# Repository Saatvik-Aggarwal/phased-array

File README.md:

# phased-array
Simulation and design of a phased array for wireless power transmission

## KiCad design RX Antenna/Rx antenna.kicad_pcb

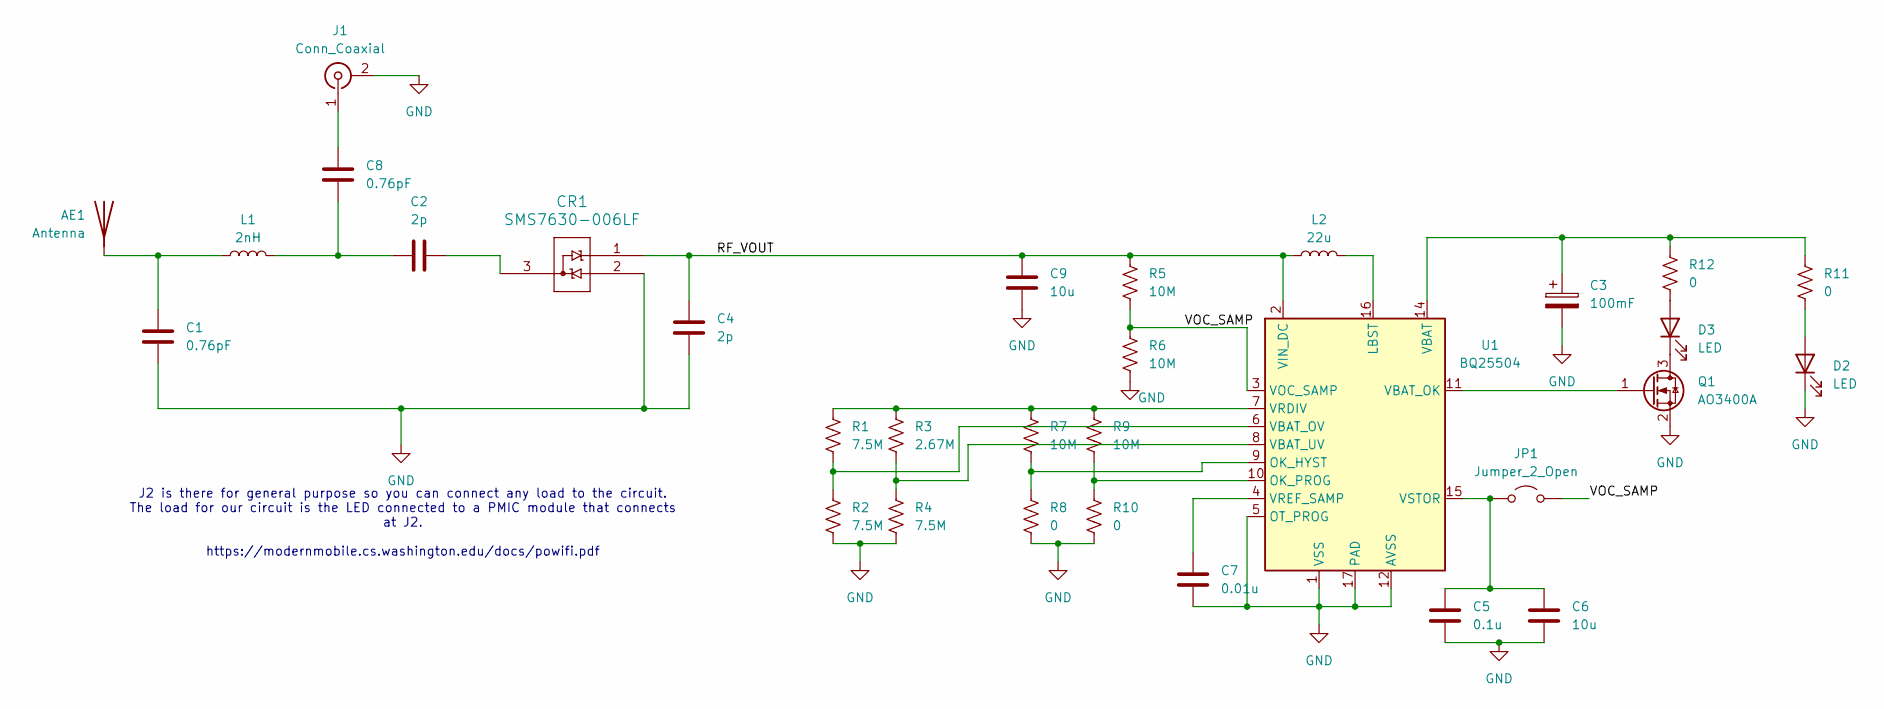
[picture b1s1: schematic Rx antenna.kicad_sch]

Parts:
AE1: Antenna; AperturePatch
C1: 0.76pF; C_0201_0603Metric_Pad0.64x0.40mm_HandSolder
C2, C4: 2p; C_0201_0603Metric_Pad0.64x0.40mm_HandSolder
C3: 100mF; CP_Radial_D10.0mm_P5.00mm
C5: 0.1u; C_0603_1608Metric_Pad1.08x0.95mm_HandSolder
C6, C9: 10u; C_0603_1608Metric_Pad1.08x0.95mm_HandSolder
C7: 0.01u; C_0603_1608Metric_Pad1.08x0.95mm_HandSolder
C8: 0.76pF; C_0201_branch
CR1: SMS7630-006LF; SOT-23
D2, D3: LED; LED_0603_1608Metric_Pad1.05x0.95mm_HandSolder
J1: Conn_Coaxial; U.FL_Hirose_U.FL-R-SMT-1_Vertical
JP1: Jumper_2_Open; SolderJumper-2_P1.3mm_Open_RoundedPad1.0x1.5mm
L1: 2nH; L_0201_0603Metric_Pad0.64x0.40mm_HandSolder
L2: 22u; L_1210_3225Metric_Pad1.42x2.65mm_HandSolder
Q1: AO3400A; SOT-23
R1, R2, R4: 7.5M; R_0603_1608Metric_Pad0.98x0.95mm_HandSolder
R3: 2.67M; R_0603_1608Metric_Pad0.98x0.95mm_HandSolder
R5, R6, R7, R9: 10M; R_0603_1608Metric_Pad0.98x0.95mm_HandSolder
R8, R10, R11, R12: 0; R_0603_1608Metric_Pad0.98x0.95mm_HandSolder
U1: BQ25504; VQFN-16-1EP_3x3mm_P0.5mm_EP1.68x1.68mm

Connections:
/RF_VOUT: C4.1, C9.1, CR1.1, L2.1, R5.1, U1.2 (VIN_DC)
/VOC_SAMP: JP1.2 (B), R5.2, R6.1, U1.3 (VOC_SAMP)
GND: C1.2, C3.2, C4.2, C5.2, C6.2, C7.2, C9.2, CR1.2, D2.1 (K), J1.2 (Ext), Q1.2 (S), R2.2, R4.2, R6.2, R8.2, R10.2, U1.1 (VSS), U1.5 (OT_PROG), U1.12 (AVSS), U1.13 (VSS), U1.17 (PAD)
unnamed: AE1.1 (A_1), C1.1, L1.1
unnamed: C2.1, C8.1, L1.2
unnamed: C2.2, CR1.3
unnamed: D2.2 (A), R11.2
unnamed: D3.2 (A), R12.2
unnamed: D3.1 (K), Q1.3 (D)
unnamed: C8.2, J1.1 (In)
unnamed: C5.1, C6.1, JP1.1 (A), U1.15 (VSTOR)
unnamed: Q1.1 (G), U1.11 (VBAT_OK)
unnamed: L2.2, U1.16 (LBST)
unnamed: R7.2, R8.1, U1.9 (OK_HYST)
unnamed: R9.2, R10.1, U1.10 (OK_PROG)
unnamed: C3.1, R11.1, R12.1, U1.14 (VBAT)
unnamed: R1.2, R2.1, U1.6 (VBAT_OV)
unnamed: R3.2, R4.1, U1.8 (VBAT_UV)
unnamed: R1.1, R3.1, R7.1, R9.1, U1.7 (VRDIV)
unnamed: C7.1, U1.4 (VREF_SAMP)

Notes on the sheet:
J2 is there for general purpose so you can connect any load to the circuit. The load for our circuit is the LED connected to a PMIC module that connects at J2. https://modernmobile.cs.washington.edu/docs/powifi.pdf

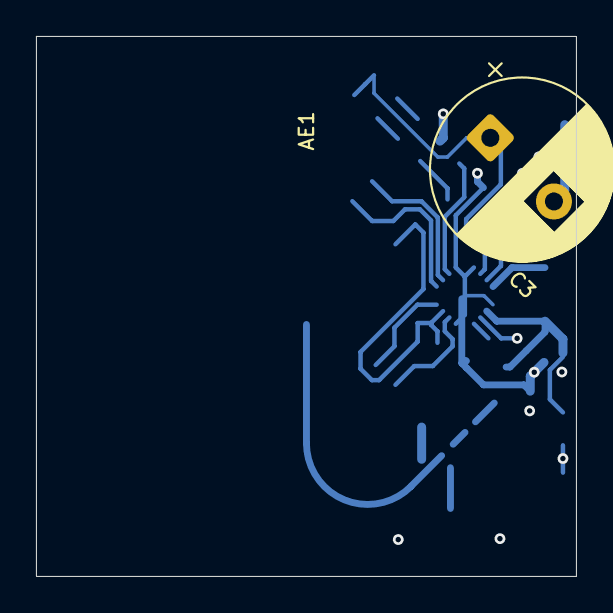
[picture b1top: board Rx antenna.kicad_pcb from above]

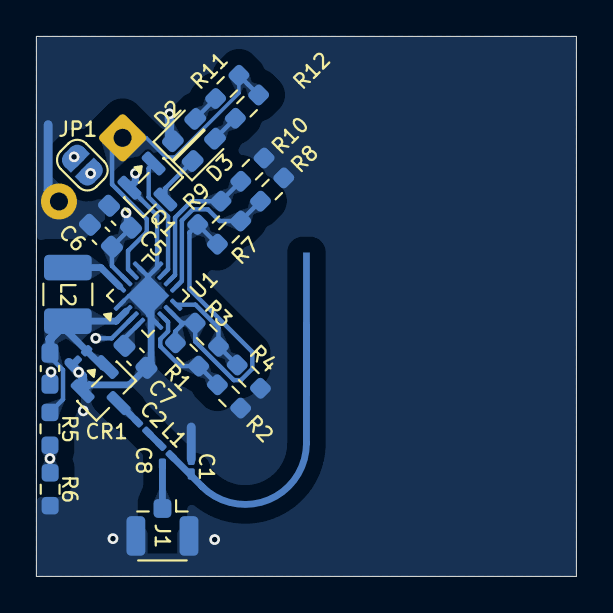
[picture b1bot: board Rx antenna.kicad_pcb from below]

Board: 4 copper layers, 30.0 x 30.0 mm, 31 parts (29 on the bottom side), 20 nets.

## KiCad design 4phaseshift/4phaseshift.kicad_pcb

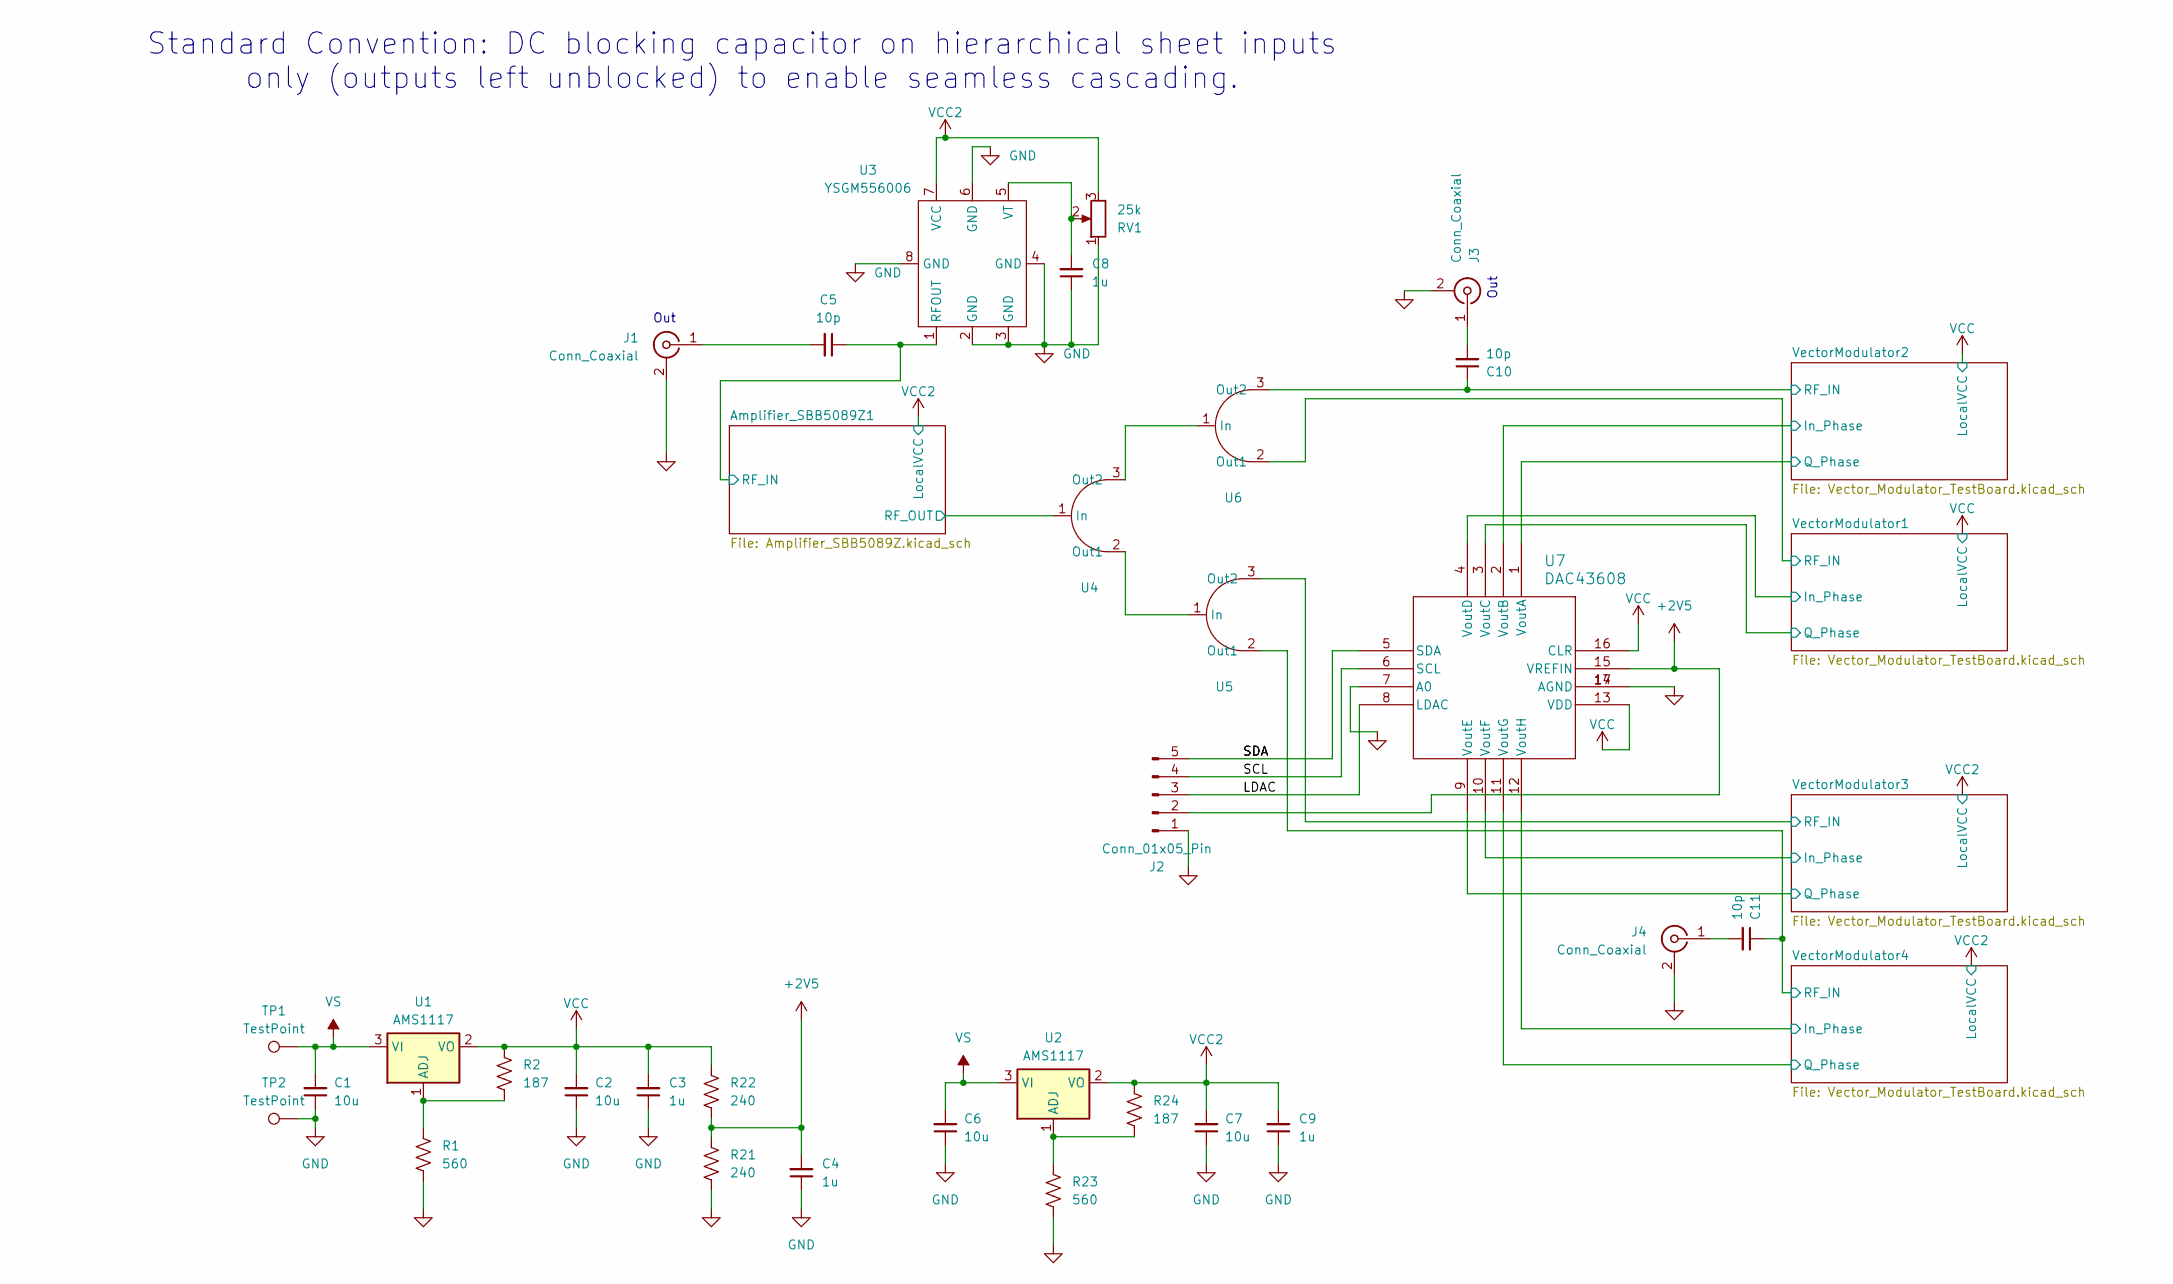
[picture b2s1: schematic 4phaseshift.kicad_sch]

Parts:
C1, C2, C6, C7: 10u; C_0603_1608Metric_Pad1.08x0.95mm_HandSolder
C3, C4, C8, C9: 1u; C_0603_1608Metric_Pad1.08x0.95mm_HandSolder
C5, C10, C11: 10p; C_0201_branch
J1, J3, J4: Conn_Coaxial; U.FL_Hirose_U.FL-R-SMT-1_Vertical
J2: Conn_01x05_Pin; PinHeader_1x05_P2.54mm_Vertical
R1, R23: 560; R_0603_1608Metric_Pad0.98x0.95mm_HandSolder
R2, R24: 187; R_0603_1608Metric_Pad0.98x0.95mm_HandSolder
R21, R22: 240; R_0603_1608Metric_Pad0.98x0.95mm_HandSolder
RV1: 25k; Potentiometer_Bourns_3386X_Horizontal
TP1, TP2: TestPoint; PinHeader_1x01_P2.54mm_Vertical
U1, U2: AMS1117; SOT-223-3_TabPin2
U3: YSGM556006; Innotion9070
U4, U5, U6: T_Splitter
U7: DAC43608; WQFN-16-1EP_3x3mm_P0.5mm_EP1.68x1.68mm

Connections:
+2V5: C4.2, J2.2, R21.1, R22.2, U7.15 (VREFIN)
/Amplifier_SBB5089Z1/RF_IN: C5.1, U3.1 (RFOUT); also elsewhere on the board
/Amplifier_SBB5089Z1/RF_OUT: U4.1 (In); also elsewhere on the board
/LDAC: J2.3, U7.8 (LDAC)
/SCL: J2.4, U7.6 (SCL)
/VectorModulator1/IBBN: U7.4 (VoutD); also elsewhere on the board
/VectorModulator1/QBBN: U7.3 (VoutC); also elsewhere on the board
/VectorModulator1/RF_IN: U6.2 (Out1); also elsewhere on the board
/VectorModulator2/IBBN: U7.2 (VoutB); also elsewhere on the board
/VectorModulator2/QBBN: U7.1 (VoutA); also elsewhere on the board
/VectorModulator2/RF_IN: C10.1, U6.3 (Out2); also elsewhere on the board
/VectorModulator3/IBBN: U7.10 (VoutF); also elsewhere on the board
/VectorModulator3/QBBN: U7.9 (VoutE); also elsewhere on the board
/VectorModulator3/RF_IN: U5.3 (Out2); also elsewhere on the board
/VectorModulator4/IBBN: U7.12 (VoutH); also elsewhere on the board
/VectorModulator4/QBBN: U7.11 (VoutG); also elsewhere on the board
/VectorModulator4/RF_IN: C11.1, U5.2 (Out1); also elsewhere on the board
GND: C1.1, C2.1, C3.1, C4.1, C6.1, C7.1, C8.1, C9.1, J1.2 (Ext), J2.1, J3.2 (Ext), J4.2 (Ext), R1.2, R21.2, R23.2, RV1.1, TP2.1, U3.2 (GND), U3.3 (GND), U3.4 (GND), U3.6 (GND), U3.8 (GND), U7.7 (A0), U7.14 (AGND), U7.17 (AGND); also elsewhere on the board
unnamed: C5.2, J1.1 (In)
unnamed: J2.5, U7.5 (SDA)
unnamed: C10.2, J3.1 (In)
unnamed: C11.2, J4.1 (In)
unnamed: R1.1, R2.2, U1.1 (ADJ)
unnamed: R23.1, R24.2, U2.1 (ADJ)
unnamed: C8.2, RV1.2, U3.5 (VT)
unnamed: U4.2 (Out1), U5.1 (In)
unnamed: U4.3 (Out2), U6.1 (In)
VCC: C2.2, C3.2, R2.1, R22.1, U1.2 (VO), U7.13 (VDD), U7.16 (CLR); also elsewhere on the board
VCC2: C7.2, C9.2, R24.1, RV1.3, U2.2 (VO), U3.7 (VCC); also elsewhere on the board
VS: C1.2, C6.2, TP1.1, U1.3 (VI), U2.3 (VI); also elsewhere on the board

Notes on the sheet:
Out
Standard Convention: DC blocking capacitor on hierarchical sheet inputs only (outputs left unblocked) to enable seamless cascading.

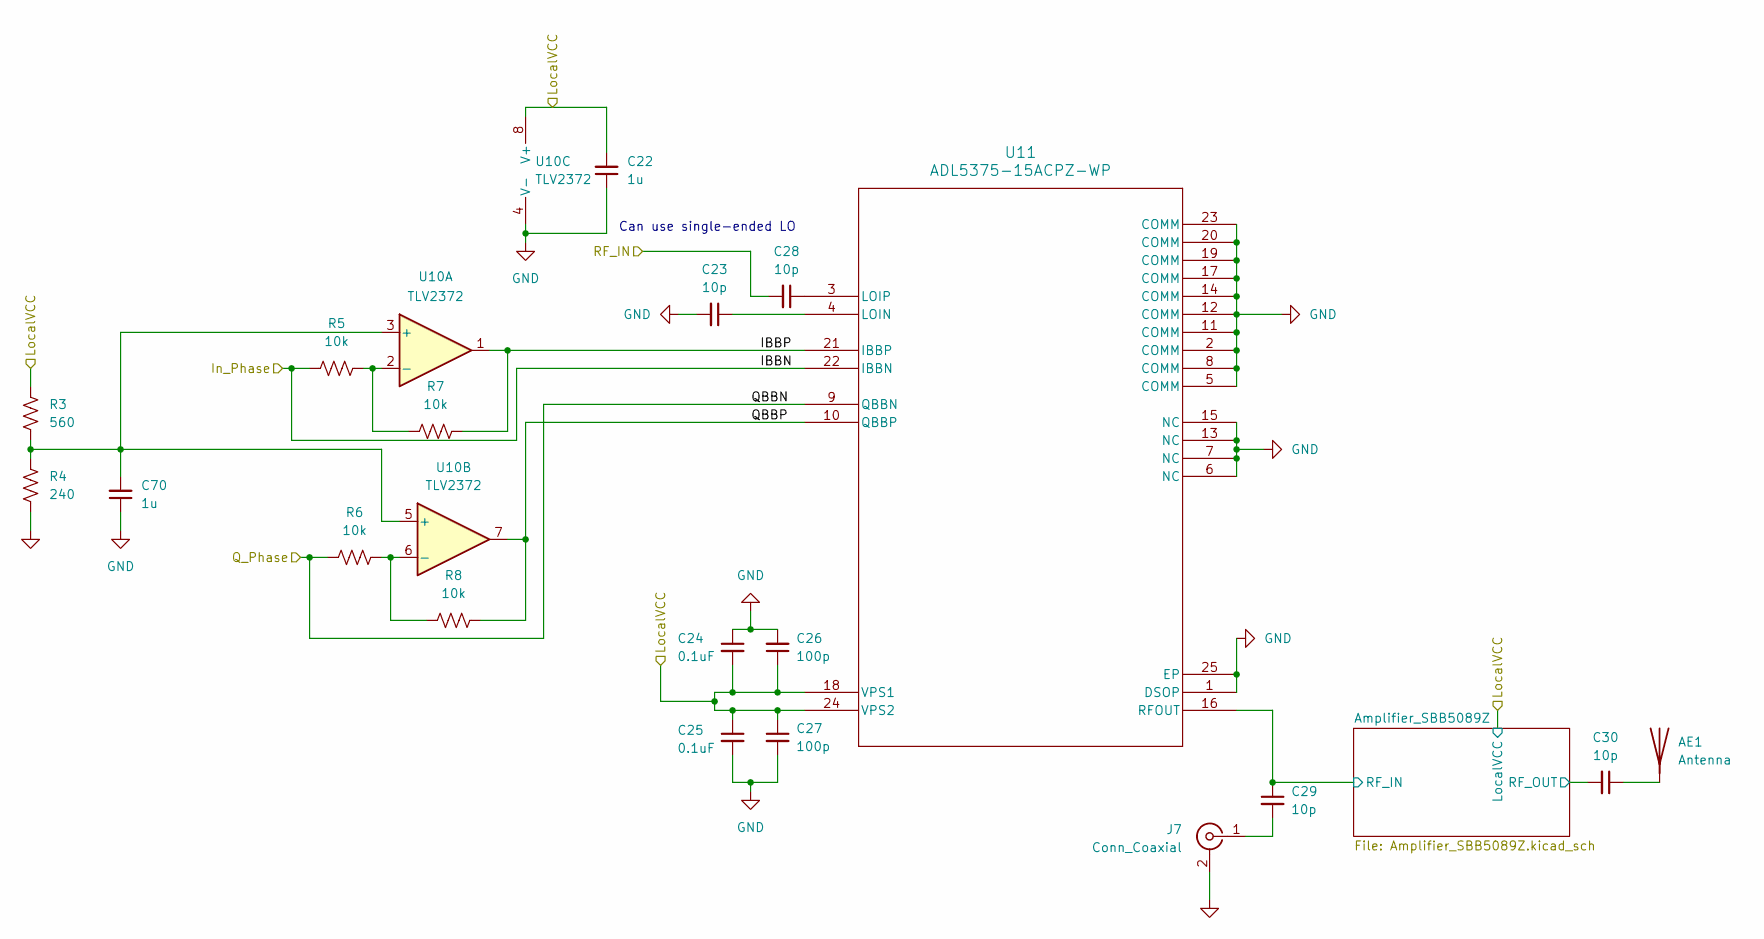
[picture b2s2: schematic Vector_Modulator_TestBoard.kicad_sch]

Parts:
AE1: Antenna; AperturePatch
C22, C70: 1u; C_0603_1608Metric_Pad1.08x0.95mm_HandSolder
C23, C28, C30: 10p; C_0201_0603Metric_Pad0.64x0.40mm_HandSolder
C24, C25: 0.1uF; C_0603_1608Metric_Pad1.08x0.95mm_HandSolder
C26, C27: 100p; C_0603_1608Metric_Pad1.08x0.95mm_HandSolder
C29: 10p; C_0201_branch
J7: Conn_Coaxial; U.FL_Hirose_U.FL-R-SMT-1_Vertical
R3: 560; R_0603_1608Metric_Pad0.98x0.95mm_HandSolder
R4: 240; R_0603_1608Metric_Pad0.98x0.95mm_HandSolder
R5, R6, R7, R8: 10k; R_0603_1608Metric_Pad0.98x0.95mm_HandSolder
U10: TLV2372; SOIC-8_3.9x4.9mm_P1.27mm
U11: ADL5375-15ACPZ-WP; LFCSP-24-1EP_4x4mm_P0.5mm_EP2.3x2.3mm_ThermalVias

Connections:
/VectorModulator1/Amplifier_SBB5089Z/RF_IN: C29.1, U11.16 (RFOUT); also elsewhere on the board
/VectorModulator1/Amplifier_SBB5089Z/RF_OUT: C30.2; also elsewhere on the board
/VectorModulator1/IBBN: R5.1, U11.22 (IBBN); also elsewhere on the board
/VectorModulator1/IBBP: R7.2, U10.1, U11.21 (IBBP)
/VectorModulator1/QBBN: R6.1, U11.9 (QBBN); also elsewhere on the board
/VectorModulator1/QBBP: R8.2, U10.7, U11.10 (QBBP)
/VectorModulator1/RF_IN: C28.2; also elsewhere on the board
GND: C22.1, C23.2, C24.1, C25.2, C26.2, C27.2, C70.1, J7.2 (Ext), R4.2, U10.4 (V-), U11.1 (DSOP), U11.2 (COMM), U11.5 (COMM), U11.6 (NC), U11.7 (NC), U11.8 (COMM), U11.11 (COMM), U11.12 (COMM), U11.13 (NC), U11.14 (COMM), U11.15 (NC), U11.17 (COMM), U11.19 (COMM), U11.20 (COMM), U11.23 (COMM), U11.25 (EP); also elsewhere on the board
unnamed: AE1.1 (A_1), C30.1
unnamed: C29.2, J7.1 (In)
unnamed: C70.2, R3.2, R4.1, U10.3 (+), U10.5 (+)
unnamed: R5.2, R7.1, U10.2 (-)
unnamed: R6.2, R8.1, U10.6 (-)
unnamed: C23.1, U11.4 (LOIN)
unnamed: C28.1, U11.3 (LOIP)
VCC: C22.2, C24.2, C25.1, C26.1, C27.1, R3.1, U10.8 (V+), U11.18 (VPS1), U11.24 (VPS2); also elsewhere on the board

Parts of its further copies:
AE2, AE3, AE4: Antenna; AperturePatch
C31, C44, C57, C71, C72, C73: 1u; C_0603_1608Metric_Pad1.08x0.95mm_HandSolder
C32, C37, C39, C45, C50, C52, C58, C63, C65: 10p; C_0201_0603Metric_Pad0.64x0.40mm_HandSolder
C33, C34, C46, C47, C59, C60: 0.1uF; C_0603_1608Metric_Pad1.08x0.95mm_HandSolder
C35, C36, C48, C49, C61, C62: 100p; C_0603_1608Metric_Pad1.08x0.95mm_HandSolder
C38, C51, C64: 10p; C_0201_branch
J8, J9, J10: Conn_Coaxial; U.FL_Hirose_U.FL-R-SMT-1_Vertical
R9, R10, R11, R12, R13, R14, R15, R16, R17, R18, R19, R20: 10k; R_0603_1608Metric_Pad0.98x0.95mm_HandSolder
R30, R32, R34: 560; R_0603_1608Metric_Pad0.98x0.95mm_HandSolder
R31, R33, R35: 240; R_0603_1608Metric_Pad0.98x0.95mm_HandSolder
U12, U15, U18: TLV2372; SOIC-8_3.9x4.9mm_P1.27mm
U13, U16, U19: ADL5375-15ACPZ-WP; LFCSP-24-1EP_4x4mm_P0.5mm_EP2.3x2.3mm_ThermalVias

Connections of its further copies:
/VectorModulator2/Amplifier_SBB5089Z/RF_IN: C38.1, U13.16 (RFOUT); also elsewhere on the board
/VectorModulator2/Amplifier_SBB5089Z/RF_OUT: C39.2; also elsewhere on the board
/VectorModulator2/IBBN: R9.1, U13.22 (IBBN); also elsewhere on the board
/VectorModulator2/IBBP: R11.2, U12.1, U13.21 (IBBP)
/VectorModulator2/QBBN: R10.1, U13.9 (QBBN); also elsewhere on the board
/VectorModulator2/QBBP: R12.2, U12.7, U13.10 (QBBP)
/VectorModulator2/RF_IN: C37.2; also elsewhere on the board
/VectorModulator3/Amplifier_SBB5089Z/RF_IN: C51.1, U16.16 (RFOUT); also elsewhere on the board
/VectorModulator3/Amplifier_SBB5089Z/RF_OUT: C52.2; also elsewhere on the board
/VectorModulator3/IBBN: R13.1, U16.22 (IBBN); also elsewhere on the board
/VectorModulator3/IBBP: R15.2, U15.1, U16.21 (IBBP)
/VectorModulator3/QBBN: R14.1, U16.9 (QBBN); also elsewhere on the board
/VectorModulator3/QBBP: R16.2, U15.7, U16.10 (QBBP)
/VectorModulator3/RF_IN: C50.2; also elsewhere on the board
/VectorModulator4/Amplifier_SBB5089Z/RF_IN: C64.1, U19.16 (RFOUT); also elsewhere on the board
/VectorModulator4/Amplifier_SBB5089Z/RF_OUT: C65.2; also elsewhere on the board
/VectorModulator4/IBBN: R17.1, U19.22 (IBBN); also elsewhere on the board
/VectorModulator4/IBBP: R19.2, U18.1, U19.21 (IBBP)
/VectorModulator4/QBBN: R18.1, U19.9 (QBBN); also elsewhere on the board
/VectorModulator4/QBBP: R20.2, U18.7, U19.10 (QBBP)
/VectorModulator4/RF_IN: C63.2; also elsewhere on the board
GND: C31.1, C32.2, C33.1, C34.2, C35.2, C36.2, C44.1, C45.2, C46.1, C47.2, C48.2, C49.2, C57.1, C58.2, C59.1, C60.2, C61.2, C62.2, C71.1, C72.1, C73.1, J8.2 (Ext), J9.2 (Ext), J10.2 (Ext), R31.2, R33.2, R35.2, U12.4 (V-), U13.1 (DSOP), U13.2 (COMM), U13.5 (COMM), U13.6 (NC), U13.7 (NC), U13.8 (COMM), U13.11 (COMM), U13.12 (COMM), U13.13 (NC), U13.14 (COMM), U13.15 (NC), U13.17 (COMM), U13.19 (COMM), U13.20 (COMM), U13.23 (COMM), U13.25 (EP), U15.4 (V-), U16.1 (DSOP), U16.2 (COMM), U16.5 (COMM), U16.6 (NC), U16.7 (NC), U16.8 (COMM), U16.11 (COMM), U16.12 (COMM), U16.13 (NC), U16.14 (COMM), U16.15 (NC), U16.17 (COMM), U16.19 (COMM), U16.20 (COMM), U16.23 (COMM), U16.25 (EP), U18.4 (V-), U19.1 (DSOP), U19.2 (COMM), U19.5 (COMM), U19.6 (NC), U19.7 (NC), U19.8 (COMM), U19.11 (COMM), U19.12 (COMM), U19.13 (NC), U19.14 (COMM), U19.15 (NC), U19.17 (COMM), U19.19 (COMM), U19.20 (COMM), U19.23 (COMM), U19.25 (EP); also elsewhere on the board
unnamed: AE2.1 (A_1), C39.1
unnamed: AE3.1 (A_1), C52.1
unnamed: AE4.1 (A_1), C65.1
unnamed: C38.2, J8.1 (In)
unnamed: C51.2, J9.1 (In)
unnamed: C64.2, J10.1 (In)
unnamed: C71.2, R30.2, R31.1, U12.3 (+), U12.5 (+)
unnamed: R9.2, R11.1, U12.2 (-)
unnamed: R10.2, R12.1, U12.6 (-)
unnamed: C32.1, U13.4 (LOIN)
unnamed: C37.1, U13.3 (LOIP)
unnamed: C72.2, R32.2, R33.1, U15.3 (+), U15.5 (+)
unnamed: R13.2, R15.1, U15.2 (-)
unnamed: R14.2, R16.1, U15.6 (-)
unnamed: C45.1, U16.4 (LOIN)
unnamed: C50.1, U16.3 (LOIP)
unnamed: C73.2, R34.2, R35.1, U18.3 (+), U18.5 (+)
unnamed: R17.2, R19.1, U18.2 (-)
unnamed: R18.2, R20.1, U18.6 (-)
unnamed: C58.1, U19.4 (LOIN)
unnamed: C63.1, U19.3 (LOIP)
VCC: C31.2, C33.2, C34.1, C35.1, C36.1, R30.1, U12.8 (V+), U13.18 (VPS1), U13.24 (VPS2); also elsewhere on the board
VCC2: C44.2, C46.2, C47.1, C48.1, C49.1, C57.2, C59.2, C60.1, C61.1, C62.1, R32.1, R34.1, U15.8 (V+), U16.18 (VPS1), U16.24 (VPS2), U18.8 (V+), U19.18 (VPS1), U19.24 (VPS2); also elsewhere on the board

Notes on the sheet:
Can use single-ended LO

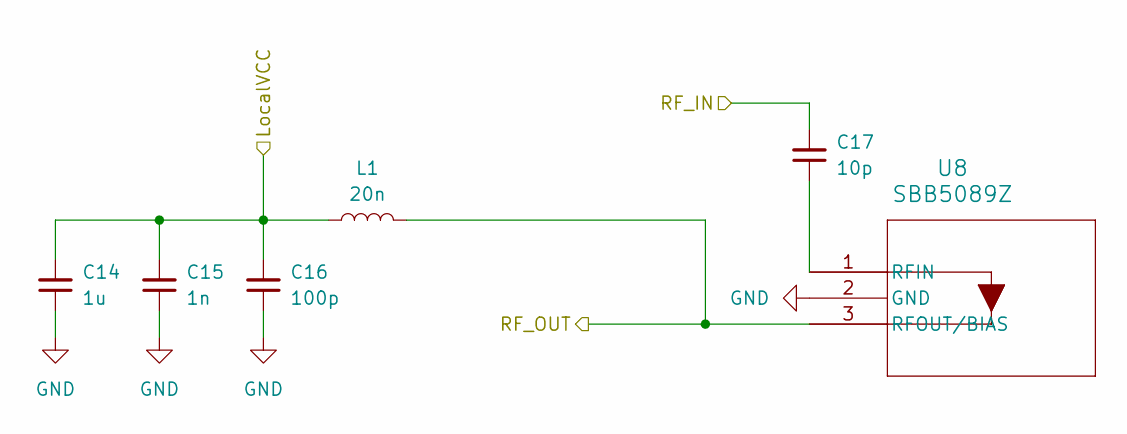
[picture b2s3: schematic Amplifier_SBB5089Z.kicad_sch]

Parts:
C14: 1u; C_0603_1608Metric_Pad1.08x0.95mm_HandSolder
C15: 1n; C_0603_1608Metric_Pad1.08x0.95mm_HandSolder
C16: 100p; C_0603_1608Metric_Pad1.08x0.95mm_HandSolder
C17: 10p; C_0201_0603Metric_Pad0.64x0.40mm_HandSolder
L1: 20n; L_0402_1005Metric_Pad0.77x0.64mm_HandSolder
U8: SBB5089Z; SOT_SBB5089Z_QOR

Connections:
/VectorModulator1/Amplifier_SBB5089Z/RF_IN: C17.2; also elsewhere on the board
/VectorModulator1/Amplifier_SBB5089Z/RF_OUT: L1.2, U8.3 (RFOUT/BIAS); also elsewhere on the board
GND: C14.1, C15.1, C16.1, U8.2 (GND); also elsewhere on the board
unnamed: C17.1, U8.1 (RFIN)
VCC: C14.2, C15.2, C16.2, L1.1; also elsewhere on the board

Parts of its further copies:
C18, C40, C53, C66: 1u; C_0603_1608Metric_Pad1.08x0.95mm_HandSolder
C19, C41, C54, C67: 1n; C_0603_1608Metric_Pad1.08x0.95mm_HandSolder
C20, C42, C55, C68: 100p; C_0603_1608Metric_Pad1.08x0.95mm_HandSolder
C21, C43, C56, C69: 10p; C_0201_0603Metric_Pad0.64x0.40mm_HandSolder
L2, L3, L4, L5: 20n; L_0402_1005Metric_Pad0.77x0.64mm_HandSolder
U9, U14, U17, U20: SBB5089Z; SOT_SBB5089Z_QOR

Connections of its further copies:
/Amplifier_SBB5089Z1/RF_IN: C21.2; also elsewhere on the board
/Amplifier_SBB5089Z1/RF_OUT: L2.2, U9.3 (RFOUT/BIAS); also elsewhere on the board
/VectorModulator2/Amplifier_SBB5089Z/RF_IN: C43.2; also elsewhere on the board
/VectorModulator2/Amplifier_SBB5089Z/RF_OUT: L3.2, U14.3 (RFOUT/BIAS); also elsewhere on the board
/VectorModulator3/Amplifier_SBB5089Z/RF_IN: C56.2; also elsewhere on the board
/VectorModulator3/Amplifier_SBB5089Z/RF_OUT: L4.2, U17.3 (RFOUT/BIAS); also elsewhere on the board
/VectorModulator4/Amplifier_SBB5089Z/RF_IN: C69.2; also elsewhere on the board
/VectorModulator4/Amplifier_SBB5089Z/RF_OUT: L5.2, U20.3 (RFOUT/BIAS); also elsewhere on the board
GND: C18.1, C19.1, C20.1, C40.1, C41.1, C42.1, C53.1, C54.1, C55.1, C66.1, C67.1, C68.1, U9.2 (GND), U14.2 (GND), U17.2 (GND), U20.2 (GND); also elsewhere on the board
unnamed: C21.1, U9.1 (RFIN)
unnamed: C43.1, U14.1 (RFIN)
unnamed: C56.1, U17.1 (RFIN)
unnamed: C69.1, U20.1 (RFIN)
VCC: C40.2, C41.2, C42.2, L3.1; also elsewhere on the board
VCC2: C18.2, C19.2, C20.2, C53.2, C54.2, C55.2, C66.2, C67.2, C68.2, L2.1, L4.1, L5.1; also elsewhere on the board

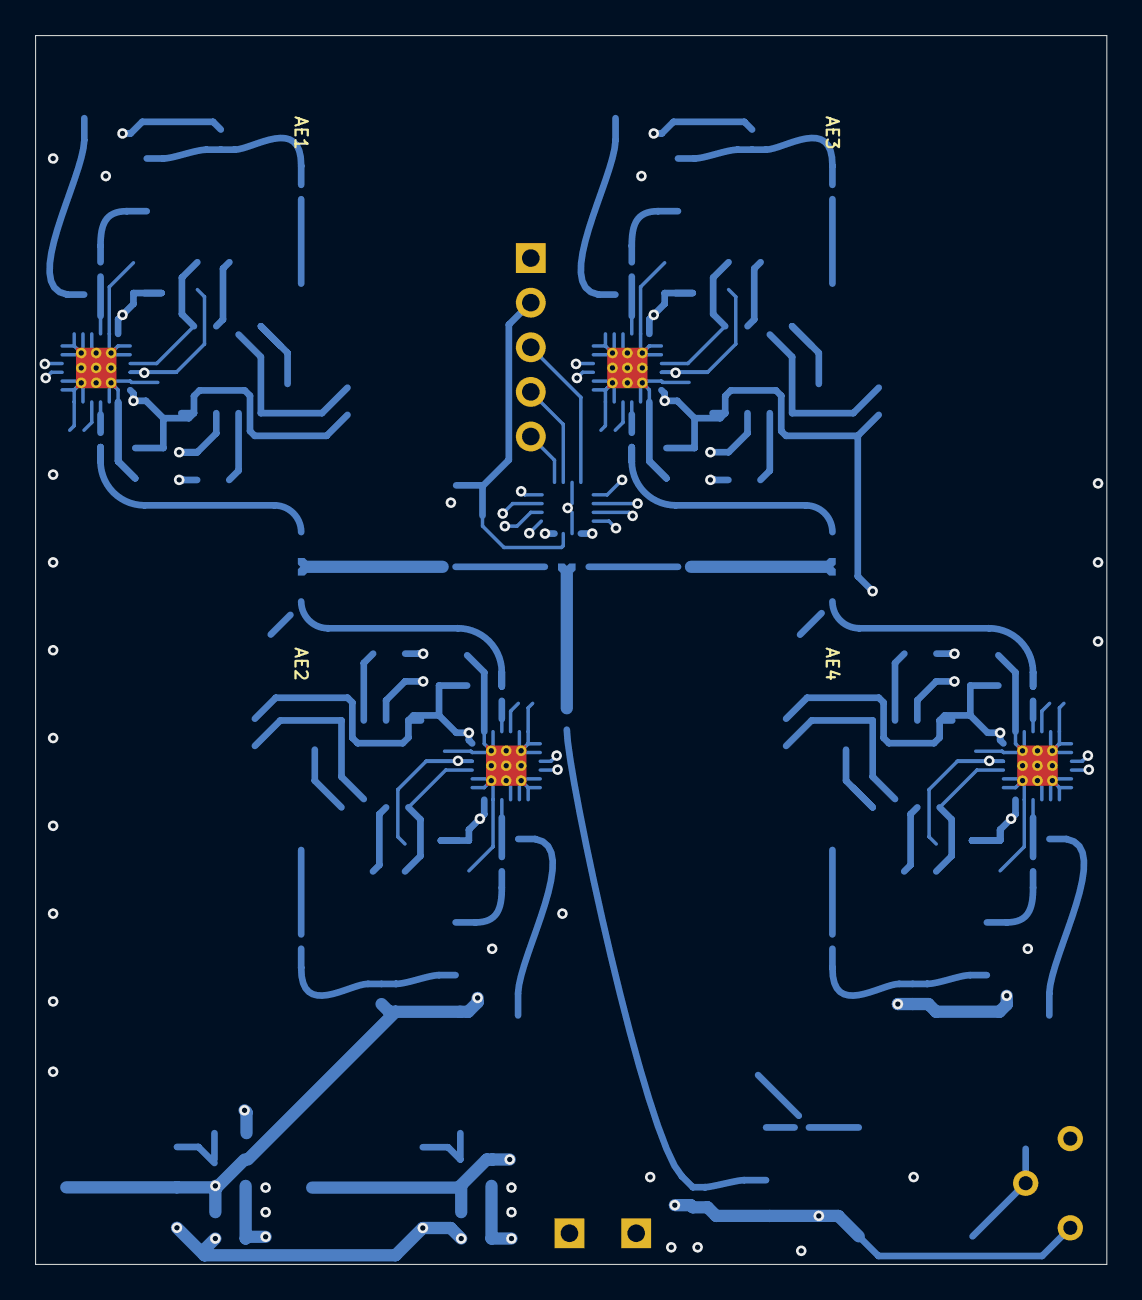
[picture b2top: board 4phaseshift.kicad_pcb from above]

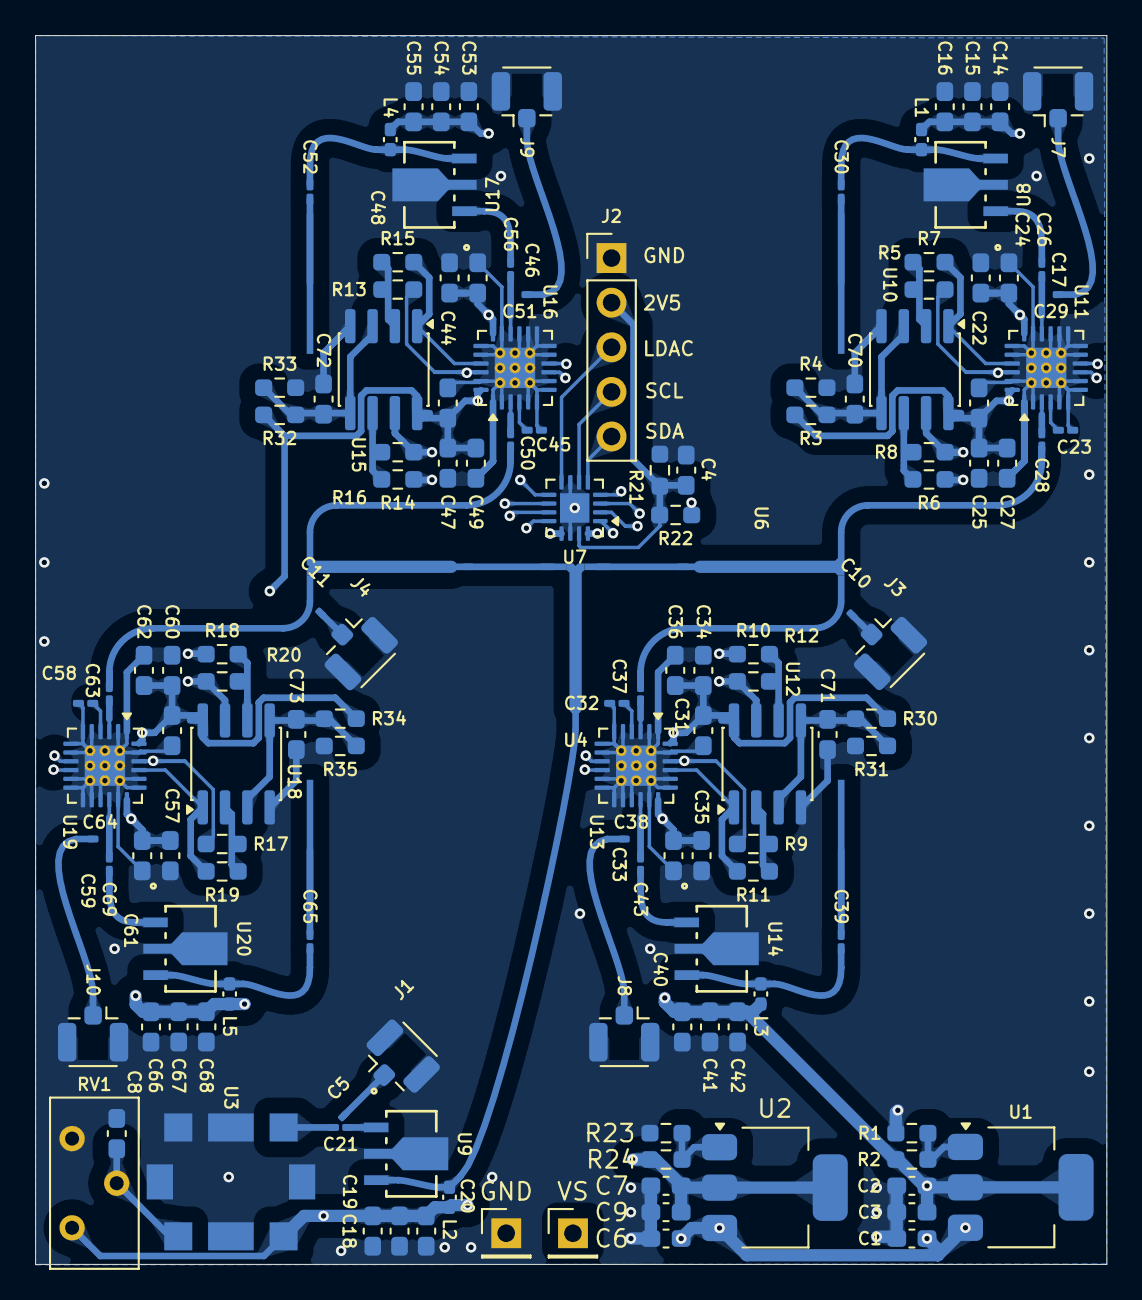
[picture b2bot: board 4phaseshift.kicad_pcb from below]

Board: 4 copper layers, 61.0 x 70.0 mm, 141 parts (137 on the bottom side), 79 nets.

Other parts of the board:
GND: TestPoint; PinHeader_1x01_P2.54mm_Vertical
VS: TestPoint; PinHeader_1x01_P2.54mm_Vertical

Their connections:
GND: GND.1; also elsewhere on the board
VS: VS.1; also elsewhere on the board

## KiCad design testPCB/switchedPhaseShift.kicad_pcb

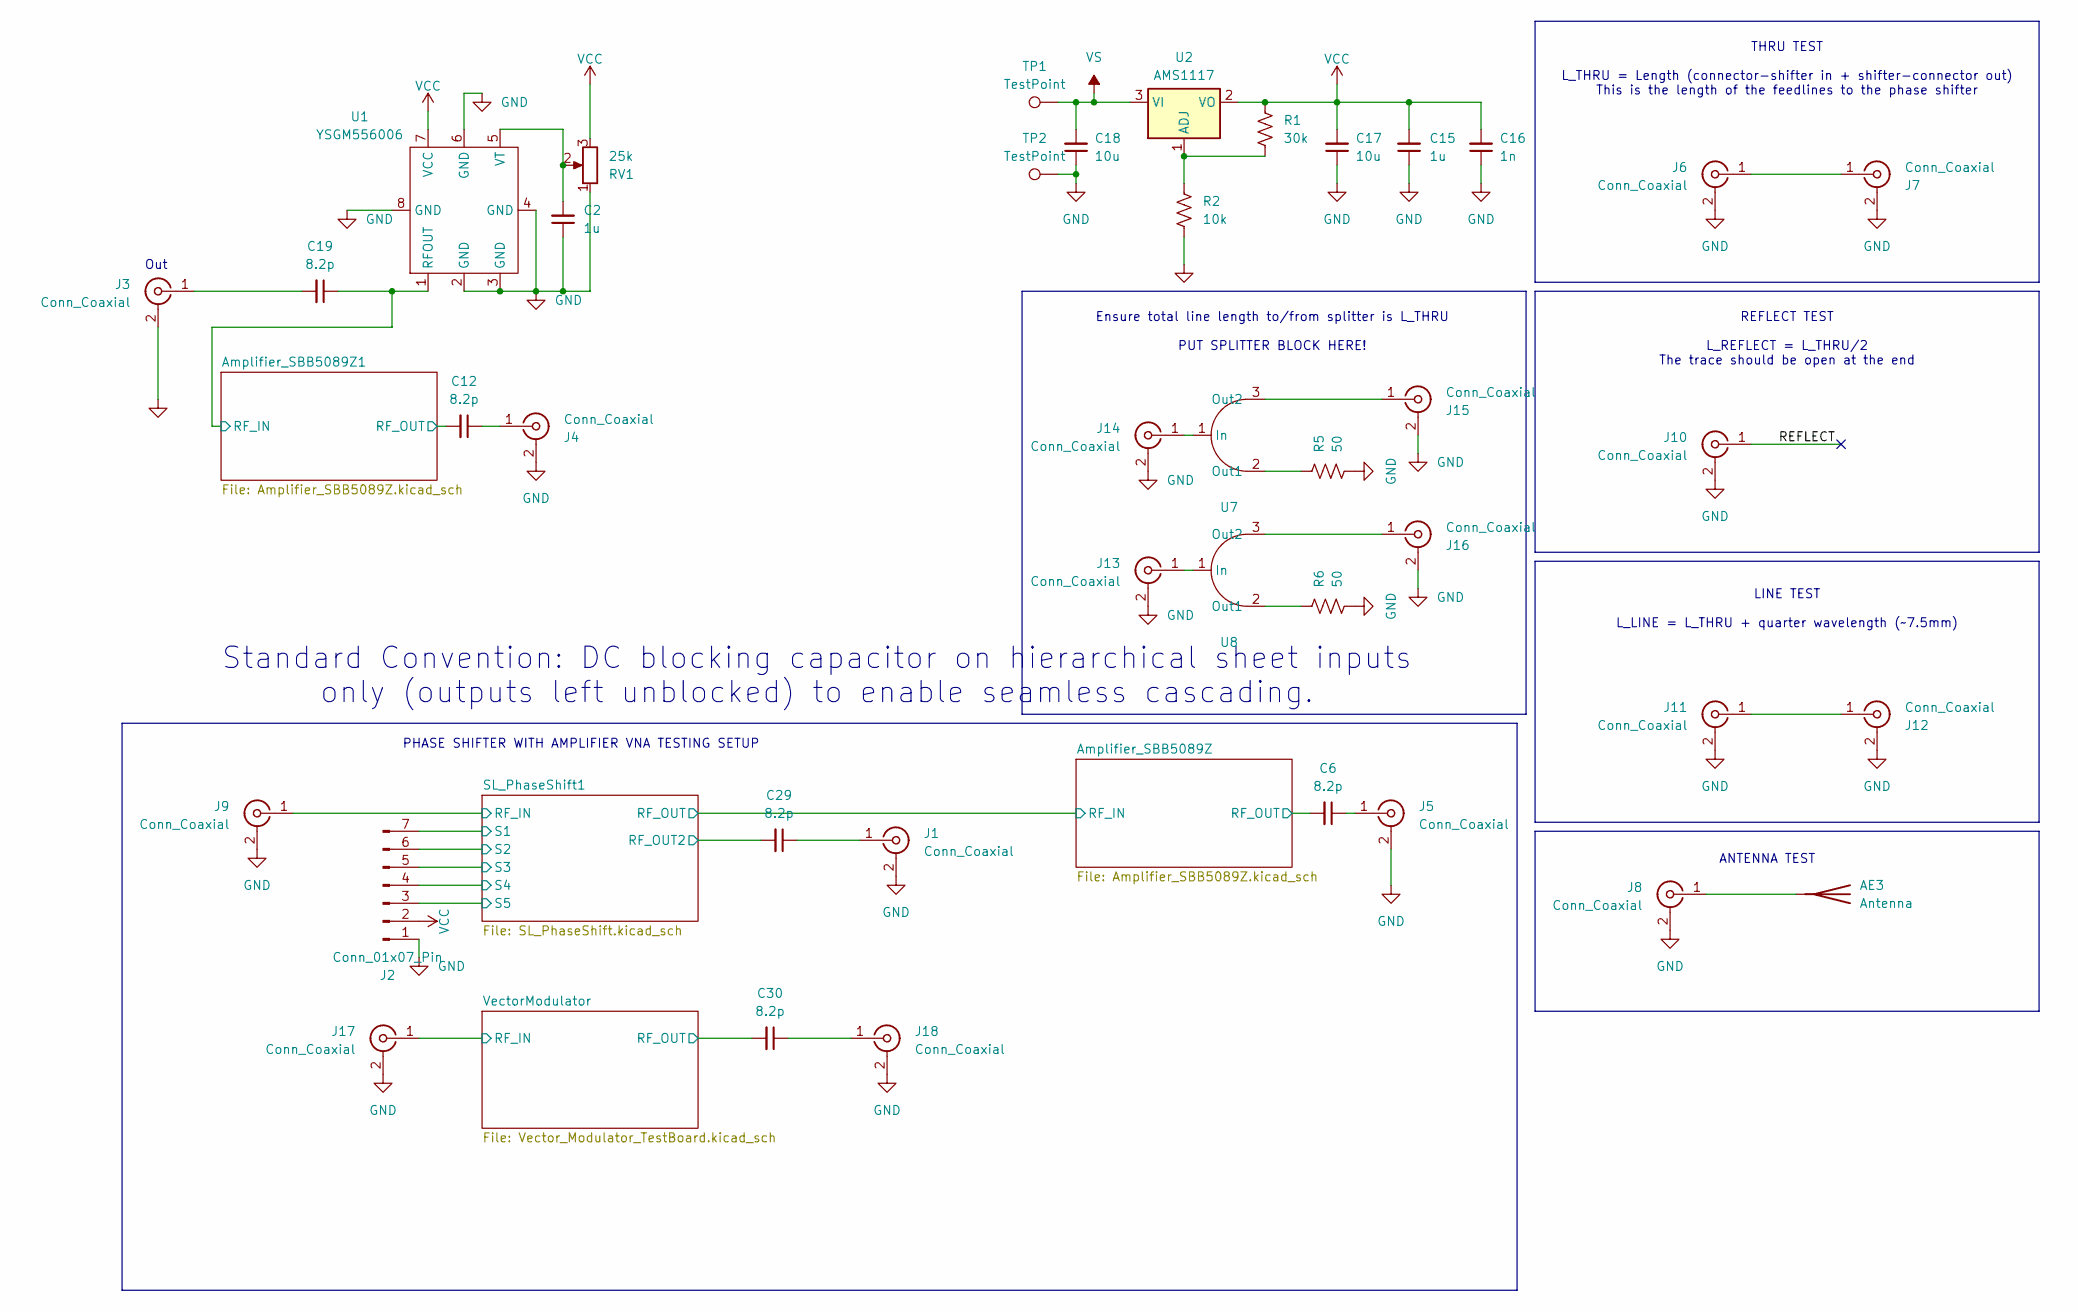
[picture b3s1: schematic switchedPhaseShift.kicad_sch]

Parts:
AE3: Antenna; AperturePatch
C2, C15: 1u; C_0603_1608Metric_Pad1.08x0.95mm_HandSolder
C6, C12, C19, C29, C30: 8.2p; C_0201_0603Metric_Pad0.64x0.40mm_HandSolder
C16: 1n; C_0603_1608Metric_Pad1.08x0.95mm_HandSolder
C17, C18: 10u; C_0603_1608Metric_Pad1.08x0.95mm_HandSolder
J1, J3, J4, J5, J6, J7, J8, J9, J10, J11, J12, J13, J14, J15, J16, J17, J18: Conn_Coaxial; U.FL_Hirose_U.FL-R-SMT-1_Vertical
J2: Conn_01x07_Pin; PinSocket_1x07_P2.54mm_Vertical
R1: 30k; R_0603_1608Metric_Pad0.98x0.95mm_HandSolder
R2: 10k; R_0603_1608Metric_Pad0.98x0.95mm_HandSolder
R5, R6: 50; R_0201_0603Metric_Pad0.64x0.40mm_HandSolder
RV1: 25k; Potentiometer_Bourns_3386X_Horizontal
TP1, TP2: TestPoint; PinHeader_1x01_P2.54mm_Vertical
U1: YSGM556006; Innotion9070
U2: AMS1117; SOT-223-3_TabPin2
U7: WilkinsonPowerDivider
U8: T_Splitter

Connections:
/Amplifier_SBB5089Z1/RF_IN: C19.1, U1.1 (RFOUT); also elsewhere on the board
/Amplifier_SBB5089Z1/RF_OUT: C12.2; also elsewhere on the board
/Amplifier_SBB5089Z/RF_OUT: C6.2; also elsewhere on the board
/REFLECT: J10.1 (In)
/SL_PhaseShift1/C1: J2.7; also elsewhere on the board
/SL_PhaseShift1/C2: J2.6; also elsewhere on the board
/SL_PhaseShift1/C3: J2.5; also elsewhere on the board
/SL_PhaseShift1/C4: J2.4; also elsewhere on the board
/SL_PhaseShift1/C5: J2.3; also elsewhere on the board
/SL_PhaseShift1/RF_IN: J9.1 (In); also elsewhere on the board
/SL_PhaseShift1/RF_OUT2: C29.2; also elsewhere on the board
/VectorModulator/RF_IN: J17.1 (In); also elsewhere on the board
/VectorModulator/RF_OUT: C30.2; also elsewhere on the board
unnamed: AE3.1 (A), J8.1 (In)
unnamed: C29.1, J1.1 (In)
unnamed: C19.2, J3.1 (In)
unnamed: C12.1, J4.1 (In)
unnamed: C6.1, J5.1 (In)
unnamed: J6.1 (In), J7.1 (In)
unnamed: J11.1 (In), J12.1 (In)
unnamed: J13.1 (In), U8.1 (In)
unnamed: J14.1 (In), U7.1 (In)
unnamed: J15.1 (In), U7.3 (Out2)
unnamed: J16.1 (In), U8.3 (Out2)
unnamed 29: C30.1, J18.1 (In); also elsewhere on the board
unnamed: C2.2, RV1.2, U1.5 (VT)
unnamed: R1.2, R2.1, U2.1 (ADJ)
unnamed: R5.1, U7.2 (Out1)
unnamed: R6.1, U8.2 (Out1)
VCC: C15.2, C16.2, C17.2, J2.2, R1.1, RV1.3, U1.7 (VCC), U2.2 (VO); also elsewhere on the board
VS: C18.2, TP1.1, U2.3 (VI); also elsewhere on the board

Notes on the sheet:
LINE TEST L_LINE = L_THRU + quarter wavelength (~7.5mm)
PHASE SHIFTER WITH AMPLIFIER VNA TESTING SETUP
ANTENNA TEST
REFLECT TEST L_REFLECT = L_THRU/2 The trace should be open at the end
Out
THRU TEST L_THRU = Length (connector-shifter in + shifter-connector out) This is the length of the feedlines to the phase shifter
Ensure total line length to/from splitter is L_THRU PUT SPLITTER BLOCK HERE!
Standard Convention: DC blocking capacitor on hierarchical sheet inputs only (outputs left unblocked) to enable seamless cascading.
